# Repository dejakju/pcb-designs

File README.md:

# pcb-designs
various pcb projects

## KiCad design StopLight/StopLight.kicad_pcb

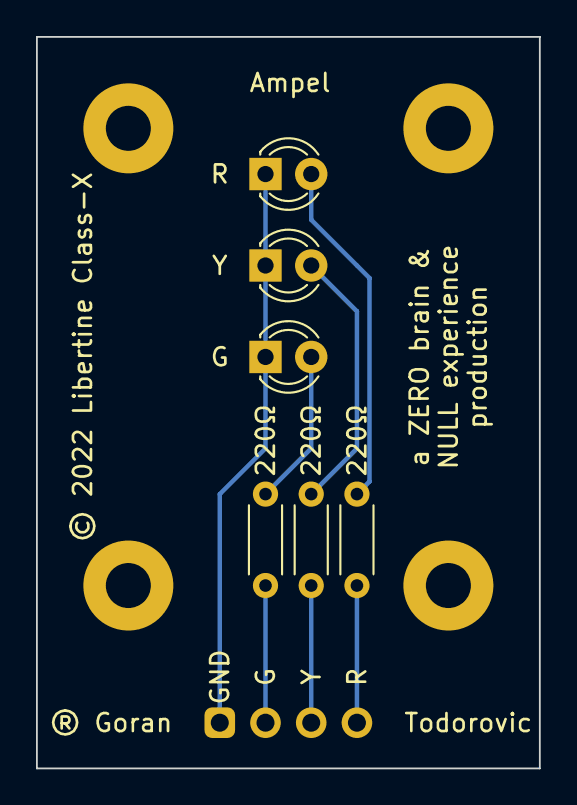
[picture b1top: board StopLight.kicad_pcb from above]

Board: 2 copper layers, 27.9 x 40.6 mm, 11 parts (1 on the bottom side), 7 nets.

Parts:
220Ω, 220Ω#2, 220Ω#3: R; R_Axial_DIN0204_L3.6mm_D1.6mm_P5.08mm_Horizontal
G: LED; LED_D3.0mm
H1, H2, H3, H4: MountingHole; MountingHole_2.5mm_Pad
J1: Conn_01x04; PinHeader_1x04_P2.54mm_Horizontal
R: LED; LED_D3.0mm
Y: LED; LED_D3.0mm

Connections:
unnamed: G.1 (K), J1.1, R.1 (K), Y.1 (K)
unnamed: 220Ω.2, G.2 (A)
unnamed: 220Ω#2.2, Y.2 (A)
unnamed: 220Ω#3.2, R.2 (A)
unnamed: 220Ω.1, J1.2
unnamed: 220Ω#2.1, J1.3
unnamed: 220Ω#3.1, J1.4

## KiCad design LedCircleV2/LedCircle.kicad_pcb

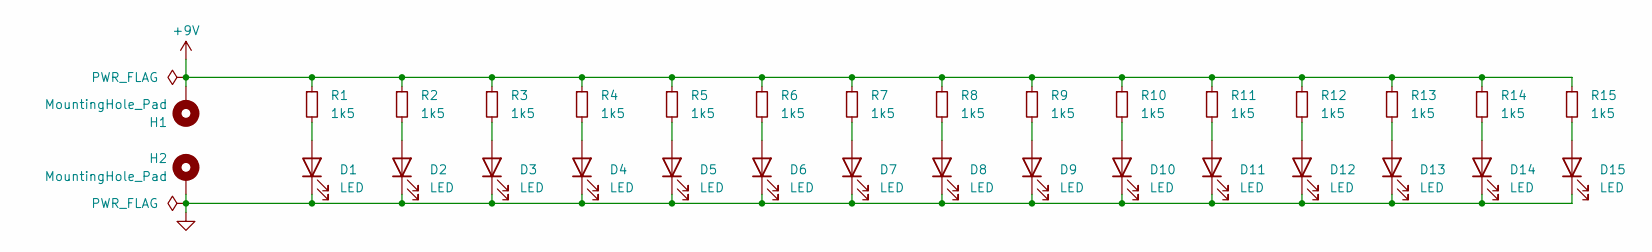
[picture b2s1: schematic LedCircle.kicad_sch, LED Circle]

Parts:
D1, D2, D3, D4, D5, D6, D7, D8, D9, D10, D11, D12, D13, D14, D15: LED; LED_D5.0mm_Clear
H1, H2: MountingHole_Pad; MountingHole_2.2mm_M2_Pad_Via
R1, R2, R3, R4, R5, R6, R7, R8, R9, R10, R11, R12, R13, R14, R15: 1k5; R_0603_1608Metric

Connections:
+9V: H1.1, R1.1, R2.1, R3.1, R4.1, R5.1, R6.1, R7.1, R8.1, R9.1, R10.1, R11.1, R12.1, R13.1, R14.1, R15.1
GND: D1.1 (K), D2.1 (K), D3.1 (K), D4.1 (K), D5.1 (K), D6.1 (K), D7.1 (K), D8.1 (K), D9.1 (K), D10.1 (K), D11.1 (K), D12.1 (K), D13.1 (K), D14.1 (K), D15.1 (K), H2.1
unnamed: D1.2 (A), R1.2
unnamed: D2.2 (A), R2.2
unnamed: D3.2 (A), R3.2
unnamed: D4.2 (A), R4.2
unnamed: D5.2 (A), R5.2
unnamed: D6.2 (A), R6.2
unnamed: D7.2 (A), R7.2
unnamed: D8.2 (A), R8.2
unnamed: D9.2 (A), R9.2
unnamed: D10.2 (A), R10.2
unnamed: D11.2 (A), R11.2
unnamed: D12.2 (A), R12.2
unnamed: D13.2 (A), R13.2
unnamed: D14.2 (A), R14.2
unnamed: D15.2 (A), R15.2

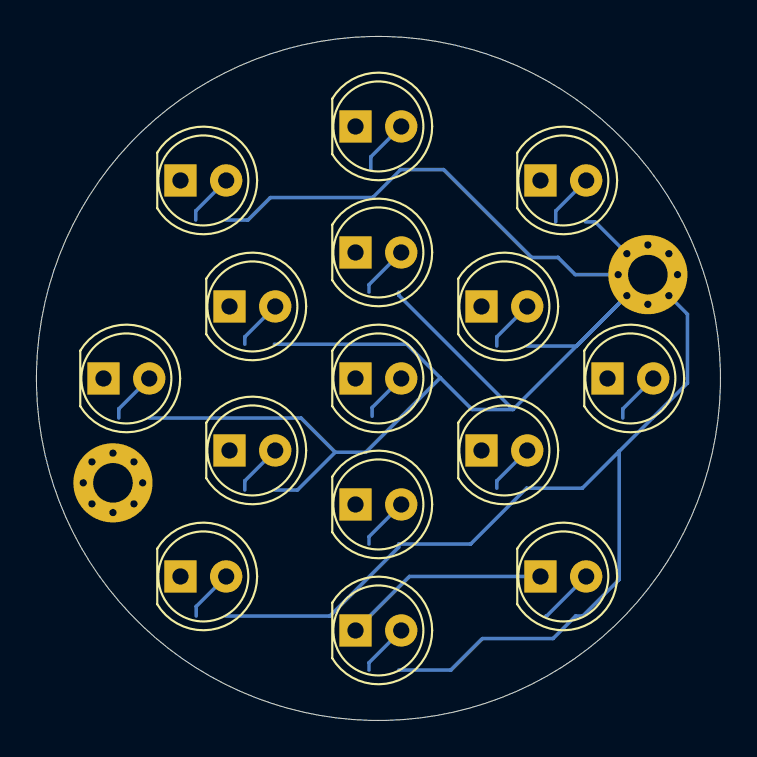
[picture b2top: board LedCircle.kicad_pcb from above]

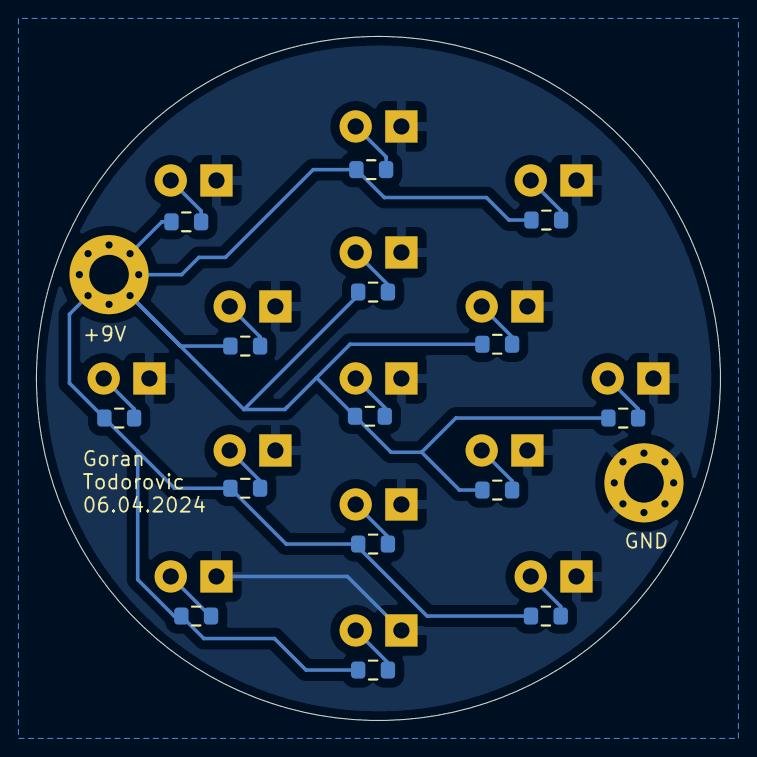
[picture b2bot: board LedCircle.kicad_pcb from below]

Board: 2 copper layers, 38.0 x 38.0 mm, 32 parts (15 on the bottom side), 17 nets.

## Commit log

2024-04-10 Initial upload

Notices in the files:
StopLight/StopLight.kicad_pcb:
© 2022 Libertine Class-X
